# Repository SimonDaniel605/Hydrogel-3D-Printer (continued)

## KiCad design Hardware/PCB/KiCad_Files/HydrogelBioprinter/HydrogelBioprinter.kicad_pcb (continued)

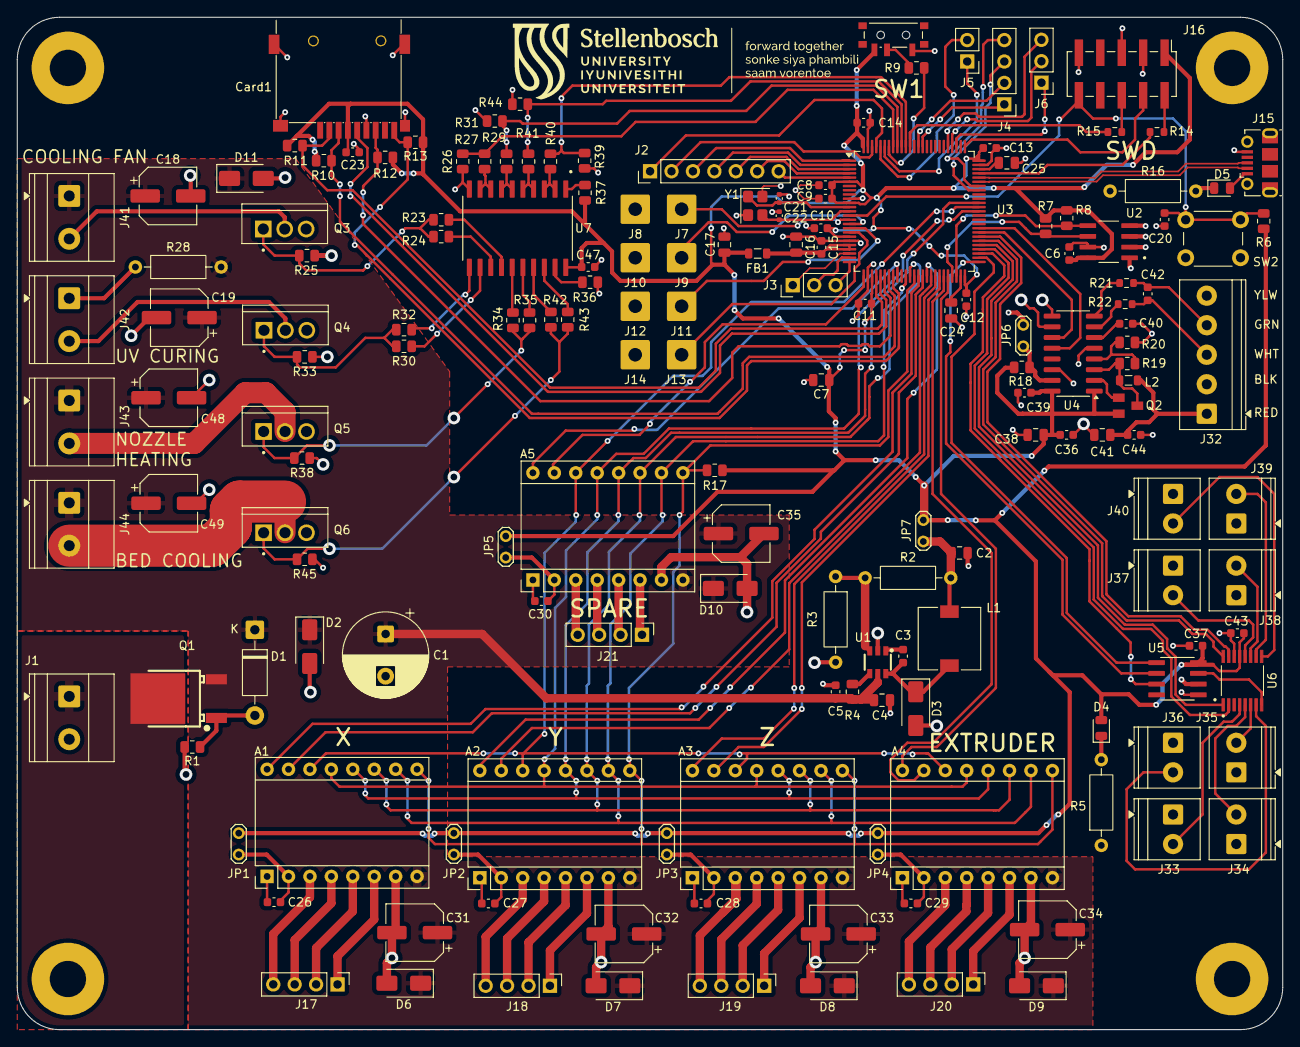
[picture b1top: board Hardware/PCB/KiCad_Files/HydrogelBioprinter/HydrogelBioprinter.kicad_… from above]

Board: 2 copper layers, 150.0 x 120.0 mm, 173 parts (0 on the bottom side), 154 nets.

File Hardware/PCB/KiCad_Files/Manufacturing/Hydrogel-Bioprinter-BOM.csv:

"Reference,""Qty"",""Value"",""Footprint"",""Description"",""LCSC Part"",""MANUFACTURER"""
"C2,""1"",""22u"",""Capacitor_SMD:C_0805_2012Metric"",""Unpolarized capacitor"",""C29277"",""Samsung Electro-Mechanics"""
"C3,C15,""2"",""10n"",""Capacitor_SMD:C_0603_1608Metric"",""Unpolarized capacitor"",""C1589"",""Samsung Electro-Mechanics"""
"C4,C7,C38,C41,""4"",""10u"",""Capacitor_SMD:C_0805_2012Metric"",""Unpolarized capacitor"",""C15850"",""Samsung Electro-Mechanics"""
"C5,C6,C8,C9,C10,C11,C12,C13,C14,C20,C23,C26,C27,C28,C29,C30,C36,C37,C39,C40,C42,C43,C44,C47,""24"",""100n"",""Capacitor_SMD:C_0603_1608Metric"",""Unpolarized capacitor"",""C1591"",""Samsung Electro-Mechanics"""
"C16,C17,""2"",""1u"",""Capacitor_SMD:C_0805_2012Metric"",""Unpolarized capacitor"",""C28323"",""Samsung Electro-Mechanics"""
"C18,C19,C31,C32,C33,C34,C35,C48,C49,""9"",""100u"",""Capacitor_SMD:CP_Elec_6.3x7.7"",""Polarized capacitor"",""C3339"",""Honor Elec"""
"C21,C22,""2"",""10p"",""Capacitor_SMD:C_0402_1005Metric"",""Unpolarized capacitor"",""C76945"",""muRata"""
"C24,C25,""2"",""2.2uF"",""Capacitor_SMD:C_0805_2012Metric"",""Unpolarized capacitor"",""C1731"",""Samsung Electro-Mechanics"""
"Card1,""1"",""TF-015"",""TF-SMD_TF-015:TF-SMD_TF-015"",""-35?~+85? 2mm Connector and Ejector MicroSD Card (TF Card) Push-Push SMD SD Card / Memory Card Connector ROHS"",""C113206"",""SOFNG"""
"D2,D6,D7,D8,D9,D10,D11,""7"",""SMAJ16A"",""Diode_SMD:D_SMA"",""400W unidirectional Transient Voltage Suppressor, 16.0Vr, SMA(DO-214AC)"",""C74561"",""Littelfuse"""
"D3,""1"",""SS34"",""Diode_SMD:D_SMA"",""40V 3A Schottky Diode, SMA"",""C8678"",""MDD(Microdiode Semiconductor)"""
"D4,""1"",""GREEN"",""LED_SMD:LED_0805_2012Metric"",""Light emitting diode"",""C2297"",""Hubei KENTO Elec"""
"D5,""1"",""BLUE"",""LED_SMD:LED_0805_2012Metric"",""Light emitting diode"",""C2987526"",""EVERLIGHT"""
"FB1,""1"",""120R"",""Inductor_SMD:L_0805_2012Metric"",""Ferrite bead"",""C5671"",""Sunlord"""
"J15,""1"",""USB_B_Micro"",""Connector_USB:USB_Micro-B_Molex-105017-0001"",""USB Micro Type B connector"",""C136000"",""MOLEX"""
"J16,""1"",""Conn_02x05_Odd_Even"",""Connector_PinHeader_2.54mm:PinHeader_2x05_P2.54mm_Vertical_SMD"",""Generic connector, double row, 02x05, odd/even pin numbering scheme (row 1 odd numbers, row 2 even numbers), script generated (kicad-library-utils/schlib/autogen/connector/)"",""C5160779"",""DEALON"""
"L1,""1"",""4.7u"",""Inductor_SMD:L_7.3x7.3_H4.5"",""Inductor"",""C514806"",""YJYCOIN"""
"L2,""1"",""3.3uH"",""Inductor_SMD:L_0805_2012Metric"",""Inductor"",""C162585"",""muRata"""
"Q1,""1"",""AOD4185_C400894"",""AOD4185:TO-252-3_L6.6-W6.1-P4.57-LS9.9-BR-CW"",""40V 40A 62.5W 15m?@10V 3V@250uA 1 P-Channel TO-252(DPAK) MOSFETs ROHS"",""C400894"",""AOS"""
"Q2,""1"",""MMBT4403_"",""MMBT4403_:SOT23-BEC"",""40V 100@150mA,2V 300mW 600mA PNP SOT-23 Bipolar (BJT) ROHS"",""C8513"",""JSCJ"""
"R1,R17,R25,R26,R31,R33,R38,R39,R44,R45,""10"",""100k"",""Resistor_SMD:R_0805_2012Metric"",""Resistor"",""C25611"",""UNI-ROYAL"""
"R4,R6,R9,R10,R11,R12,R13,R18,R36,R37,""10"",""10k"",""Resistor_SMD:R_0805_2012Metric"",""Resistor"",""C17414"",""UNI-ROYAL"""
"R7,R8,""2"",""4.7k"",""Resistor_SMD:R_0805_2012Metric"",""Resistor"",""C26022"",""UNI-ROYAL"""
"R14,R15,""2"",""22"",""Resistor_SMD:R_0603_1608Metric"",""Resistor"",""C1203"",""UNI-ROYAL"""
"R19,""1"",""20k"",""Resistor_SMD:R_0805_2012Metric"",""Resistor"",""C4328"",""UNI-ROYAL"""
"R20,""1"",""8.2k"",""Resistor_SMD:R_0805_2012Metric"",""Resistor"",""C17828"",""UNI-ROYAL"""
"R21,R22,""2"",""100R"",""Resistor_SMD:R_0603_1608Metric"",""Resistor"",""C22775"",""UNI-ROYAL"""
"R23,R24,R27,R29,R30,R32,R34,R35,R40,R41,R42,R43,""12"",""47R"",""Resistor_SMD:R_0805_2012Metric"",""Resistor"",""C17714"",""UNI-ROYAL"""
"SW1,""1"",""SW_SPDT"",""Button_Switch_SMD:SW_SPDT_PCM12"",""Switch, single pole double throw"",""C221841"",""C&K"""
"U1,""1"",""AP3211KTR-G1"",""AP3211KTR-G1:AP3211KTR-G1"",""Buck Adjustable 810mV~15V 1.5A 4.5V~18V SOT-23-6 DC-DC Converters ROHS"",""C154863"",""DIODES"""
"U2,""1"",""M24C64-WMN6TP"",""M24C64-WMN6TP:SOIC127P600X175-8N"",""64Kbit I2C SOIC-8 EEPROM ROHS"",""C7999"",""STMicroelectronics"""
"U3,""1"",""STM32F407VGT6"",""Package_QFP:LQFP-100_14x14mm_P0.5mm"",""STMicroelectronics Arm Cortex-M4 MCU, 1024KB flash, 192KB RAM, 168 MHz, 1.8-3.6V, 82 GPIO, LQFP100"",""C12345"",""ST"""
"U4,""1"",""HX711"",""Package_SO:SOP-16_3.9x9.9mm_P1.27mm"",""24-Bit Analog-to-Digital Converter (ADC) for Weight Scales"",""C43656"",""Avia Semicon (Xiamen)"""
"U5,""1"",""MAX6675ISA_"",""MAX6675ISA_:SOIC127P600X175-8N"",""3V~5.5V 12 SPI SOIC-8 ADCs/DACs - Special Purpose ROHS"",""C16030"",""MAXIM"""
"U6,""1"",""TMUX1208PWR"",""TMUX1208PWR:SOP65P640X120-16N"",""5? 1 8:1 TSSOP-16 Analog Switches, Multiplexers ROHS"",""C494728"",""TI"""
"U7,""1"",""SN74HC245DWR"",""SN74HC245DWR:SOIC127P1030X265-20N"",""SOIC-20-300mil Buffers, Drivers, Receivers, Transceivers ROHS"",""C10093"",""TI"""
"Y1,""1"",""16MHz"",""Crystal:Crystal_SMD_3225-4Pin_3.2x2.5mm"",""Four pin crystal, GND on pins 2 and 4"",""C112972"",""YXC Crystal Oscillators"""

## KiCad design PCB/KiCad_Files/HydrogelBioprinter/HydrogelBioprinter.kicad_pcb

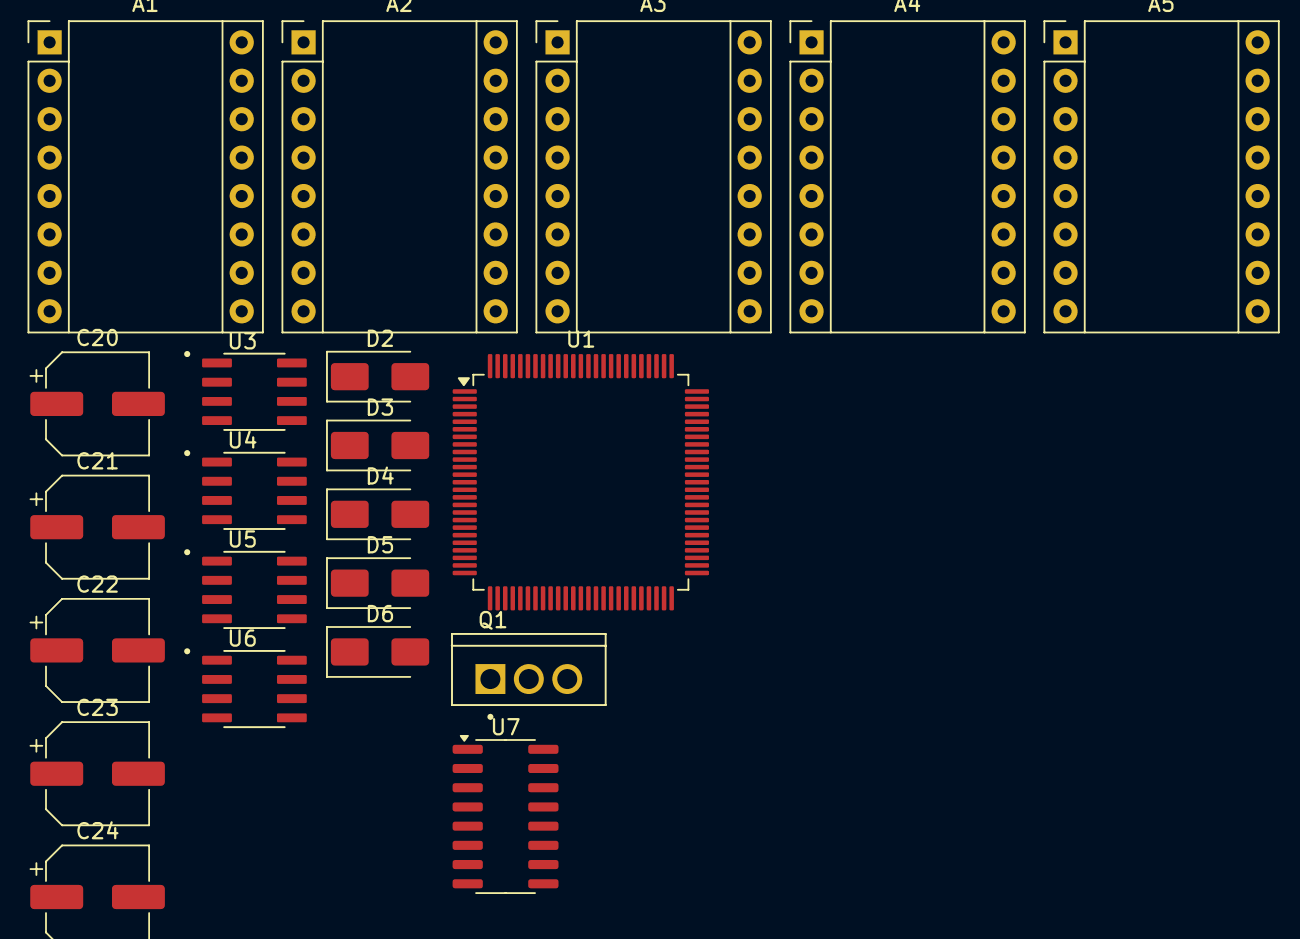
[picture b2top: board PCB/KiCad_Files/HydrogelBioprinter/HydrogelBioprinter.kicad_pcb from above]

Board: 2 copper layers, 22 parts (0 on the bottom side), 4 nets, no tracks yet.

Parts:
A1, A2, A3, A4, A5: Pololu_Breakout_DRV8825; Pololu_Breakout-16_15.2x20.3mm
C20, C21, C22, C23, C24: C_Polarized; CP_Elec_6.3x7.7
D2, D3, D4, D5, D6: SMAJ28A; D_SMA
Q1: RFP30N06LE; TRANS_RFP30N06LE
U1: STM32F407VGT6; LQFP-100_14x14mm_P0.5mm
U3, U4, U5, U6: MAX6675ISA_; SOIC127P600X175-8N
U7: HX711; SOP-16_3.9x9.9mm_P1.27mm

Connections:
+3.3V: A1.2 (~FLT), A2.2 (~FLT), A3.2 (~FLT), A4.2 (~FLT), A5.2 (~FLT), U1.6 (VBAT), U1.11 (VDD), U1.19 (VDD), U1.28 (VDD), U1.50 (VDD), U1.75 (VDD), U1.100 (VDD)
+24V: A1.8 (VMOT), A2.8 (VMOT), A3.8 (VMOT), A4.8 (VMOT), A5.8 (VMOT), C20.1, C21.1, C22.1, C23.1, C24.1, D2.1 (A1), D3.1 (A1), D4.1 (A1), D5.1 (A1), D6.1 (A1)
/~EN1: A1.9 (~EN), A2.9 (~EN), A3.9 (~EN), A4.9 (~EN), A5.9 (~EN)
GND: A1.1 (GND), A1.7 (GND), A2.1 (GND), A2.7 (GND), A3.1 (GND), A3.7 (GND), A4.1 (GND), A4.7 (GND), A5.1 (GND), A5.7 (GND), C20.2, C21.2, C22.2, C23.2, C24.2, D2.2 (A2), D3.2 (A2), D4.2 (A2), D5.2 (A2), D6.2 (A2), U1.10 (VSS), U1.20 (VSSA), U1.27 (VSS), U1.74 (VSS), U1.99 (VSS)

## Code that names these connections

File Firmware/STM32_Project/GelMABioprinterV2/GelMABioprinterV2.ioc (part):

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Mcu.Name=STM32F407V(E-G)Tx
Mcu.Package=LQFP100
Mcu.UserName=STM32F407VGTx
PA11.Mode=Device_Only
PA11.Signal=USB_OTG_FS_DM
PA12.Mode=Device_Only
PA12.Signal=USB_OTG_FS_DP
PA13.Mode=Serial_Wire
PA13.Signal=SYS_JTMS-SWDIO
PA14.Mode=Serial_Wire
PA14.Signal=SYS_JTCK-SWCLK
PA3.GPIOParameters=GPIO_Speed
PA3.GPIO_Speed=GPIO_SPEED_FREQ_LOW
PA3.Signal=GPIO_Output
PA4.GPIOParameters=PinState,GPIO_PuPd,GPIO_Label
PA4.GPIO_Label=SPI1_CS
PA4.GPIO_PuPd=GPIO_PULLUP
PA4.PinState=GPIO_PIN_SET
PA4.Signal=GPIO_Output
PA5.GPIOParameters=GPIO_PuPd
PA5.GPIO_PuPd=GPIO_PULLUP
PA5.Mode=Full_Duplex_Master
PA5.Signal=SPI1_SCK
PA6.GPIOParameters=GPIO_PuPd
PA6.GPIO_PuPd=GPIO_PULLUP
PA6.Mode=Full_Duplex_Master
PA6.Signal=SPI1_MISO
PA7.GPIOParameters=GPIO_PuPd
PA7.GPIO_PuPd=GPIO_PULLUP
PA7.Mode=Full_Duplex_Master
PA7.Signal=SPI1_MOSI
PB1.Signal=GPIO_Output
PB10.Mode=I2C
PB10.Signal=I2C2_SCL
PB11.Mode=I2C
PB11.Signal=I2C2_SDA
PB15.Signal=GPIO_Output
PB2.Signal=GPIO_Output
PB4.Signal=GPIO_Output
PB5.Signal=S_TIM3_CH2
PB6.Signal=S_TIM4_CH1
PB7.Signal=S_TIM4_CH2
PC0.GPIOParameters=GPIO_PuPd
PC0.GPIO_PuPd=GPIO_PULLUP
PC0.Signal=GPIO_Input
PC1.GPIOParameters=GPIO_PuPd
PC1.GPIO_PuPd=GPIO_PULLUP
PC1.Signal=GPIO_Input
PC10.Mode=Full_Duplex_Master
PC10.Signal=SPI3_SCK
PC11.Mode=Full_Duplex_Master
PC11.Signal=SPI3_MISO
PC12.Mode=Full_Duplex_Master
PC12.Signal=SPI3_MOSI
PC2.GPIOParameters=GPIO_PuPd
PC2.GPIO_PuPd=GPIO_PULLUP
PC2.Signal=GPIO_Input
PC4.GPIOParameters=GPIO_PuPd,GPIO_Label,GPIO_ModeDefaultEXTI
PC4.GPIO_Label=SPI1_CD
PC4.GPIO_ModeDefaultEXTI=GPIO_MODE_IT_RISING_FALLING
PC4.GPIO_PuPd=GPIO_PULLUP
PC4.Signal=GPXTI4
PC5.Signal=GPIO_Output
PC6.GPIOParameters=PinState
PC6.PinState=GPIO_PIN_SET
PC6.Signal=GPIO_Output
PC7.GPIOParameters=PinState
PC7.PinState=GPIO_PIN_SET
PC7.Signal=GPIO_Output
PC8.Signal=GPIO_Output
PD10.Signal=GPIO_Output
PD11.Signal=GPIO_Output
PD12.GPIOParameters=GPIO_PuPd
PD12.GPIO_PuPd=GPIO_PULLUP
PD12.Signal=GPIO_Input
PD8.GPIOParameters=PinState
PD8.PinState=GPIO_PIN_SET
PD8.Signal=GPIO_Output
PD9.Signal=GPIO_Output
PE10.Signal=GPIO_Output
PE11.GPIOParameters=GPIO_Speed
PE11.GPIO_Speed=GPIO_SPEED_FREQ_LOW
PE11.Signal=GPIO_Output
PE12.Signal=GPIO_Output
PE13.GPIOParameters=GPIO_Speed
PE13.GPIO_Speed=GPIO_SPEED_FREQ_LOW
PE13.Signal=GPIO_Output
PE14.GPIOParameters=GPIO_Speed
PE14.GPIO_Speed=GPIO_SPEED_FREQ_LOW
PE14.Signal=GPIO_Output
PE15.Signal=GPIO_Output
PE6.GPIOParameters=PinState,GPIO_PuPd
PE6.GPIO_PuPd=GPIO_NOPULL
PE6.PinState=GPIO_PIN_SET
PE6.Signal=GPIO_Output
PE7.GPIOParameters=PinState
PE7.PinState=GPIO_PIN_SET
PE7.Signal=GPIO_Output
PE8.Signal=GPIO_Output
PE9.GPIOParameters=GPIO_Speed
PE9.GPIO_Speed=GPIO_SPEED_FREQ_LOW
PE9.Signal=GPIO_Output
PH0-OSC_IN.Mode=HSE-External-Oscillator
PH0-OSC_IN.Signal=RCC_OSC_IN
PH1-OSC_OUT.Mode=HSE-External-Oscillator
PH1-OSC_OUT.Signal=RCC_OSC_OUT
RCC.HSE_VALUE=16000000
RCC.SYSCLKFreq_VALUE=168000000
RCC.SYSCLKSource=RCC_SYSCLKSOURCE_PLLCLK
board=custom

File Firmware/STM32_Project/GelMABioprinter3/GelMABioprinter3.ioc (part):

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Mcu.Name=STM32F407V(E-G)Tx
Mcu.Package=LQFP100
Mcu.UserName=STM32F407VGTx
PA11.Mode=Device_Only
PA11.Signal=USB_OTG_FS_DM
PA12.Mode=Device_Only
PA12.Signal=USB_OTG_FS_DP
PA13.Mode=Serial_Wire
PA13.Signal=SYS_JTMS-SWDIO
PA14.Mode=Serial_Wire
PA14.Signal=SYS_JTCK-SWCLK
PA3.GPIOParameters=GPIO_Speed
PA3.GPIO_Speed=GPIO_SPEED_FREQ_LOW
PA3.Signal=GPIO_Output
PA4.GPIOParameters=PinState,GPIO_PuPd,GPIO_Label
PA4.GPIO_Label=SPI1_CS
PA4.GPIO_PuPd=GPIO_PULLUP
PA4.PinState=GPIO_PIN_SET
PA4.Signal=GPIO_Output
PA5.GPIOParameters=GPIO_PuPd
PA5.GPIO_PuPd=GPIO_PULLUP
PA5.Mode=Full_Duplex_Master
PA5.Signal=SPI1_SCK
PA6.GPIOParameters=GPIO_PuPd
PA6.GPIO_PuPd=GPIO_PULLUP
PA6.Mode=Full_Duplex_Master
PA6.Signal=SPI1_MISO
PA7.GPIOParameters=GPIO_PuPd
PA7.GPIO_PuPd=GPIO_PULLUP
PA7.Mode=Full_Duplex_Master
PA7.Signal=SPI1_MOSI
PB1.Signal=GPIO_Output
PB10.Mode=I2C
PB10.Signal=I2C2_SCL
PB11.Mode=I2C
PB11.Signal=I2C2_SDA
PB12.GPIOParameters=PinState
PB12.PinState=GPIO_PIN_SET
PB12.Signal=GPIO_Output
PB13.Mode=RX_Only_Simplex_Unidirect_Master
PB13.Signal=SPI2_SCK
PB14.Mode=RX_Only_Simplex_Unidirect_Master
PB14.Signal=SPI2_MISO
PB15.Signal=GPIO_Output
PB2.Signal=GPIO_Output
PB4.Signal=GPIO_Output
PB5.Signal=S_TIM3_CH2
PB6.Signal=S_TIM4_CH1
PB7.Signal=S_TIM4_CH2
PC0.GPIOParameters=GPIO_PuPd
PC0.GPIO_PuPd=GPIO_PULLUP
PC0.Signal=GPIO_Input
PC1.GPIOParameters=GPIO_PuPd
PC1.GPIO_PuPd=GPIO_PULLUP
PC1.Signal=GPIO_Input
PC2.GPIOParameters=GPIO_PuPd
PC2.GPIO_PuPd=GPIO_PULLUP
PC2.Signal=GPIO_Input
PC4.GPIOParameters=GPIO_PuPd,GPIO_Label,GPIO_ModeDefaultEXTI
PC4.GPIO_Label=SPI1_CD
PC4.GPIO_ModeDefaultEXTI=GPIO_MODE_IT_RISING_FALLING
PC4.GPIO_PuPd=GPIO_PULLUP
PC4.Signal=GPXTI4
PC5.Signal=GPIO_Output
PC6.GPIOParameters=PinState
PC6.PinState=GPIO_PIN_SET
PC6.Signal=GPIO_Output
PC7.GPIOParameters=PinState
PC7.PinState=GPIO_PIN_SET
PC7.Signal=GPIO_Output
PC8.Signal=GPIO_Output
PD10.Signal=GPIO_Output
PD11.Signal=GPIO_Output
PD12.GPIOParameters=GPIO_PuPd
PD12.GPIO_PuPd=GPIO_PULLUP
PD12.Signal=GPIO_Input
PD8.GPIOParameters=PinState
PD8.PinState=GPIO_PIN_SET
PD8.Signal=GPIO_Output
PD9.Signal=GPIO_Output
PE10.Signal=GPIO_Output
PE11.GPIOParameters=GPIO_Speed
PE11.GPIO_Speed=GPIO_SPEED_FREQ_LOW
PE11.Signal=GPIO_Output
PE12.Signal=GPIO_Output
PE13.GPIOParameters=GPIO_Speed
PE13.GPIO_Speed=GPIO_SPEED_FREQ_LOW
PE13.Signal=GPIO_Output
PE14.GPIOParameters=GPIO_Speed
PE14.GPIO_Speed=GPIO_SPEED_FREQ_LOW
PE14.Signal=GPIO_Output
PE15.Signal=GPIO_Output
PE7.GPIOParameters=PinState
PE7.PinState=GPIO_PIN_SET
PE7.Signal=GPIO_Output
PE8.Signal=GPIO_Output
PE9.GPIOParameters=GPIO_Speed
PE9.GPIO_Speed=GPIO_SPEED_FREQ_LOW
PE9.Signal=GPIO_Output
PH0-OSC_IN.Mode=HSE-External-Oscillator
PH0-OSC_IN.Signal=RCC_OSC_IN
PH1-OSC_OUT.Mode=HSE-External-Oscillator
PH1-OSC_OUT.Signal=RCC_OSC_OUT
RCC.HSE_VALUE=8000000
RCC.SYSCLKFreq_VALUE=72000000
RCC.SYSCLKSource=RCC_SYSCLKSOURCE_PLLCLK
board=custom

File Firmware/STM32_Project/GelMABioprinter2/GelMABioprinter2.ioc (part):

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Mcu.Name=STM32F407V(E-G)Tx
Mcu.Package=LQFP100
Mcu.UserName=STM32F407VGTx
PA11.Mode=Device_Only
PA11.Signal=USB_OTG_FS_DM
PA12.Mode=Device_Only
PA12.Signal=USB_OTG_FS_DP
PA13.Mode=Serial_Wire
PA13.Signal=SYS_JTMS-SWDIO
PA14.Mode=Serial_Wire
PA14.Signal=SYS_JTCK-SWCLK
PB3.Signal=SYS_JTDO-SWO
PD11.Signal=GPIO_Output
PD12.Signal=GPIO_Input
PD13.GPIOParameters=PinState
PD13.PinState=GPIO_PIN_SET
PD13.Signal=GPIO_Output
PE0.Signal=GPIO_Output
PE1.Signal=GPIO_Output
PH0-OSC_IN.Mode=HSE-External-Oscillator
PH0-OSC_IN.Signal=RCC_OSC_IN
PH1-OSC_OUT.Mode=HSE-External-Oscillator
PH1-OSC_OUT.Signal=RCC_OSC_OUT
RCC.HSE_VALUE=8000000
RCC.SYSCLKFreq_VALUE=72000000
RCC.SYSCLKSource=RCC_SYSCLKSOURCE_PLLCLK
board=custom

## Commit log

2025-06-05 Added driver connections to PCB KiCad Schematic
2025-06-06 Additions to the KiCad PCB Schematic
2025-06-09 Finished Drivers and Thermocouple Amplifier connections in KiCad Schematic
2025-07-03 Further KiCad Schematic Design Progress
2025-07-10 Schematic Update, PCB preliminary layout, Machine Design addition, and LaTeX report addition
2025-07-10 Git Test
2025-07-13 Progress on Gantry Concept Designs
2025-07-16 Gantry Concept 2 Completion
2025-07-16 Gantry Concept 1 Completion and PCB schematic update
2025-07-17 Final gantry machine design progress
2025-07-18 Further final extruder design progress
2025-07-19 Final gantry design progress
2025-07-21 Rough PCB Design Completion
2025-07-23 Report Progress
2025-07-23 Final PCB Design
2025-07-27 PCB Catastrophe
2025-07-29 Final machine design complete
2025-07-31 Mechanical drawing pack for manufactured parts prepared
2025-07-31 The start of the firmware dev stage!
2025-08-01 Stepper firmware successfully turned a NEMA 17
2025-08-05 DXF files prepared for Fabrinox quote
2025-10-24 Deadline update (minimal set, Experiments excluded)
2025-10-24 report images
2025-10-24 Ignore .xcf files
2025-10-24 phase 2
2025-10-24 some more trials
2025-10-24 the rest of the experimental results
2025-11-03 Demo Preparation
2025-11-04 Further demo prep
2025-11-11 Demo Date Drawing Near
2025-11-11 2 days out
2025-11-11 2 days
2025-11-11 Stop tracking large video assets and ignore them going forward
2025-11-11 Restore Demo and Images folder structure (videos removed)
2025-11-11 Add demo assets (PPTX, images, task generator, small videos)
2025-11-11 Add all demo assets, images, small videos
2025-11-11 Ignore the large MOV file
2025-11-11 Add final demo MP4 video
2026-06-01 Temperature feedback updates
